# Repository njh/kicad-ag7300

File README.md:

# AG7300 KiCad Files

This repository contains a KiCad symbol and footprint for the [SilverTel Ag7300](https://silvertel.com/ag7300/) DC-DC converter module.

## Usage

To use the AG7300 symbol and footprint in your own KiCad project:

1. Clone this repository or download the symbol and footprint files.
2. Add the `.kicad_sym` and `.kicad_mod` files to your project's library paths:
   - Go to **Preferences > Manage Symbol Libraries** to add the symbol.
   - Go to **Preferences > Manage Footprint Libraries** to add the footprint.
3. You can now place the AG7300 module in your schematic and PCB layout as needed.

## Schematic and PCB

Also included is a schematic similar to the official Ag7300 evaluation board.

I was planning on making a board to install in a [Ubiquiti USW-24-POE](https://techspecs.ui.com/unifi/switching/usw-24-poe) network switch, which would allow it to operate from a 24V battery:

However, I decided not to proceed further with this design as it was too similar to the evaluation board.

## KiCad Version

Tested with **KiCad 9.0.1**

## License

This project is licensed under the [MIT License](LICENSE).

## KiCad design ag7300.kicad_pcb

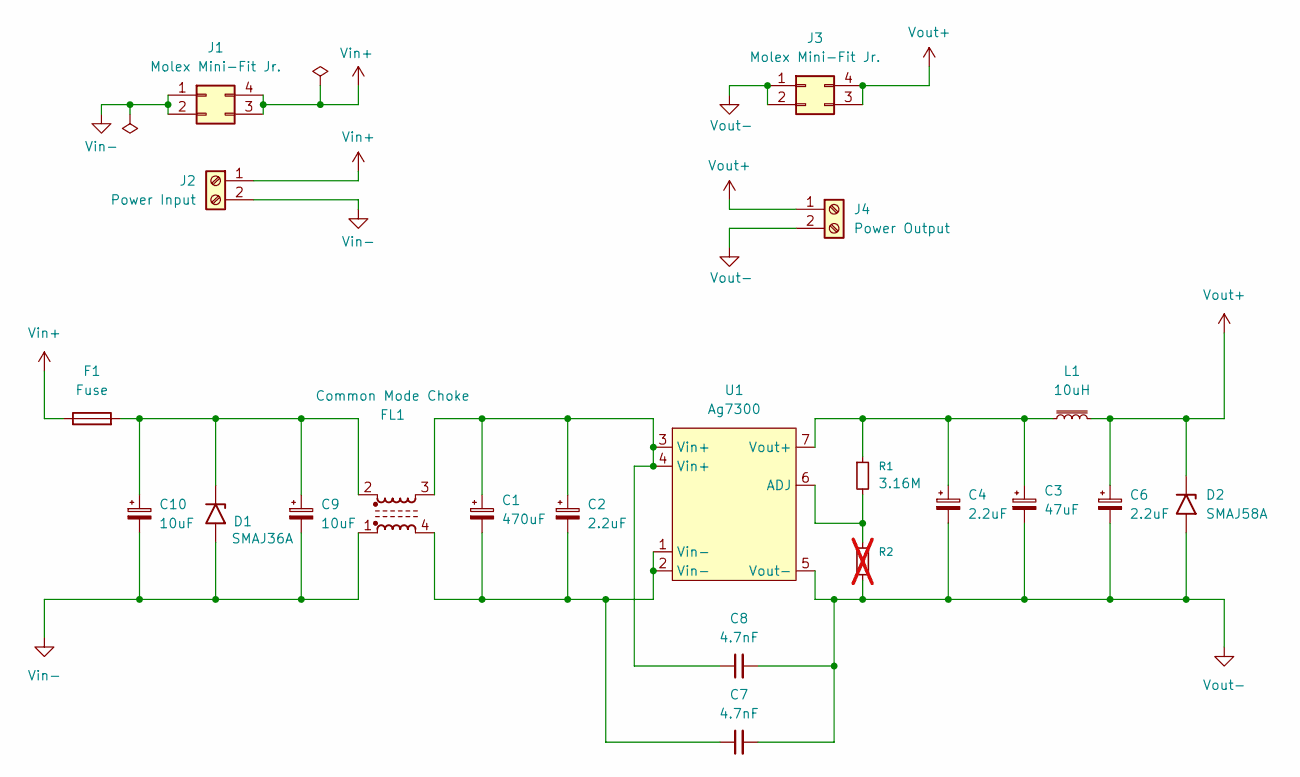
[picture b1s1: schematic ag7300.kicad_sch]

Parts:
C1: 470uF; CP_Radial_D13.0mm_P5.00mm
C2, C4, C6: 2.2uF; C_Disc_D6.0mm_W4.4mm_P5.00mm
C3: 47uF; CP_Radial_D10.0mm_P5.00mm
C7, C8: 4.7nF; C_Disc_D14.5mm_W5.0mm_P10.00mm
C9, C10: 10uF; CP_Radial_D5.0mm_P2.00mm
D1: SMAJ36A; D_SMA
D2: SMAJ58A; D_SMA
F1: Fuse; Fuseholder_Cylinder-5x20mm_Schurter_0031_8201_Horizontal_Op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
FL1: Common Mode Choke; CM2545X171B
J1, J3: Molex Mini-Fit Jr.; Molex_Mini-Fit_Jr_5566-04A_2x02_P4.20mm_Vertical
J2: Power Input; TerminalBlock_Phoenix_MKDS-1,5-2_1x02_P5.00mm_Horizontal
J4: Power Output; TerminalBlock_Phoenix_MKDS-1,5-2_1x02_P5.00mm_Horizontal
L1: 10uH; L_Radial_D10.0mm_P5.00mm_Fastron_07M
R1: 3.16M; R_Axial_DIN0207_L6.3mm_D2.5mm_P7.62mm_Horizontal
R2: 3.16M; R_Axial_DIN0207_L6.3mm_D2.5mm_P7.62mm_Horizontal; not fitted
U1: Ag7300

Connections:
unnamed: C1.1, C2.1, C8.1, FL1.3, U1.3 (Vin+), U1.4 (Vin+)
unnamed: C1.2, C2.2, C7.1, FL1.4, U1.1 (Vin-), U1.2 (Vin-)
unnamed: C9.1, C10.1, D1.1 (A1), F1.2, FL1.2
unnamed: R1.2, R2.1, U1.6 (ADJ)
unnamed: C3.1, C4.1, L1.1, R1.1, U1.7 (Vout+)
Vin+: F1.1, J1.3, J1.4, J2.1
Vin-: C9.2, C10.2, D1.2 (A2), FL1.1, J1.1, J1.2, J2.2
Vout+: C6.1, D2.1 (A1), J3.3, J3.4, J4.1, L1.2
Vout-: C3.2, C4.2, C6.2, C7.2, C8.2, D2.2 (A2), J3.1, J3.2, J4.2, R2.2, U1.5 (Vout-)

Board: 2 copper layers, 21 parts (0 on the bottom side), 9 nets, no tracks yet.

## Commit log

2025-04-05 Added Symbol for Ag7300
2025-04-05 Added PDF docs from silvertel.com
2025-04-12 Added Bill of Materials for EvalAg7300 board - Extracted JPEG of table from PDF - Converted JPEG to CSV using https://table.studio/convert/jpeg/to/csv
2025-04-23 Added KiCad footprint file
2025-04-26 Added main board schematic and project files
2025-05-30 Added CM2545X171B part to library
2025-05-30 Mapped symbols to footprints
2025-05-30 Renamed project
2025-05-30 Added PCB file
2025-05-30 Project rename fixes
2025-05-30 Updated repo with status of project
